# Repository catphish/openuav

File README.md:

# OpenUAV
OpenUAV is an open source flight controller for multirotors with
a focus on FPV. It is currently in active development.

# Features
* ACRO and ANGLE flight modes
* DSHOT
* ELRS
* Blackbox flight recorder
* USB configuration tool
* Canvas OSD

# Roadmap
* Tidy up and comment all current code
* USB configuration tool
* More OSD options

# Dependencies

## ArchLinux-based distributions

```sh
sudo pacman -Sy arm-none-eabi-binutils arm-none-eabi-gcc arm-none-eabi-newlib \
                dfu-util \
                stlink
```

# Configurator

The USB configurator can be used to configure the quad, and also to download blackbox
logs.

## Configuration

You can view the current configuration by running `configurator get`.

The commands to set configuration are a little cryptic. Use command `configurator set x y z`, where `x` is the
categry number, `y` is the specific entry number, and `z` is the value to set. Please refer to the following file
for the category and entry numbers: https://github.com/catphish/openuav/blob/master/configurator/usb.h

## Motor configuration

The motor configuration is also not very intuitive, but works as follows. First select "props in" `configurator set 3 5 0`
or "props out" `configurator set 3 5 1`.

Next, map the motor outputs using the command: `configurator set 3 x y`, where `x` is the motor output pin (1-4), and `y` is
a corner of the quad according to the following table:

```
0: no output
1: rear left
2: front right
3: front left
4: rear right
```

* NOTE: Due to the way air mode currently works, motors set to zero outout will still spin at minimum RPM. This needs fixing.

## Black Box

Data will be recorded to the black box any time the quad is armed and will continue until the memory
is full (approx 10 minutes flight time). You can erase the black box with `configurator erase`.

You can download the blackbox data with `configurator read > data.csv`. The CSV can be processed
with any tool of your choosing but I find kst2 to be the best.

# Basic Tuning Guide

Tuning should be done in acro mode at a rate you are comfortable with. I use a rate
of 1200 (840 dps) for this process.

## Part 1 - P term

Set the I and D terms to zero so that they don't interfere. Start with a low value (P=50).
Increase P until the quad is sufficiently responsive to stick inputs. You can expect a
little bounceback.
In the 5 inch development quad, the P value is 120.

## Part 2 - D term

Increase the D term only as much as is required to prevent the bounceback.
In the 5 inch development quad, the D value is 150.

## Part 3 - I term

Increase the I term only as much as is required to prevent drift. You may find that this
needs to be increased more when flying in strong wind. Higher values will make the quad
more stable but will introduce some bouncenback when performing flips.
In the 5 inch development quad, the I value is 50.

## Part 4 - Z rates

There is currently no specific process for tuning the Z rates. Values of 200 and 200
for P and I seem to work in most cases. If there is yaw drift then it may be necessary
to increase one or the other. Increase the I term in the case of slow drift or the P
term in the case of sudden yaw disruption.

# Tuning Examples

## TBS Source One V5 5" - 2306/2555KV Motors at 4S

```
Angle rate: 1000
Acro rate: 1000
P: 100
I: 80
D: 100
Yaw P: 200
Yaw I: 100
Expo: 60
Yaw expo: 60
Throttle gain: 80
Throttle min: 200
```

## iFlight iX3 Racer V1 3" - 1104/5250KV Motors at 3S

THIS TUNE IS STILL UNDERGOING TESTING

```
Angle rate (sR): 670
Acro rate (sr): 670
P (sp): x
I (si): x
D (sd): x
Yaw P (sy): 220
Yaw I (sY): 200
Expo (se): 25
Yaw expo (sE): 30
Throttle gain (st): 80
Throttle min (sT): 100
```

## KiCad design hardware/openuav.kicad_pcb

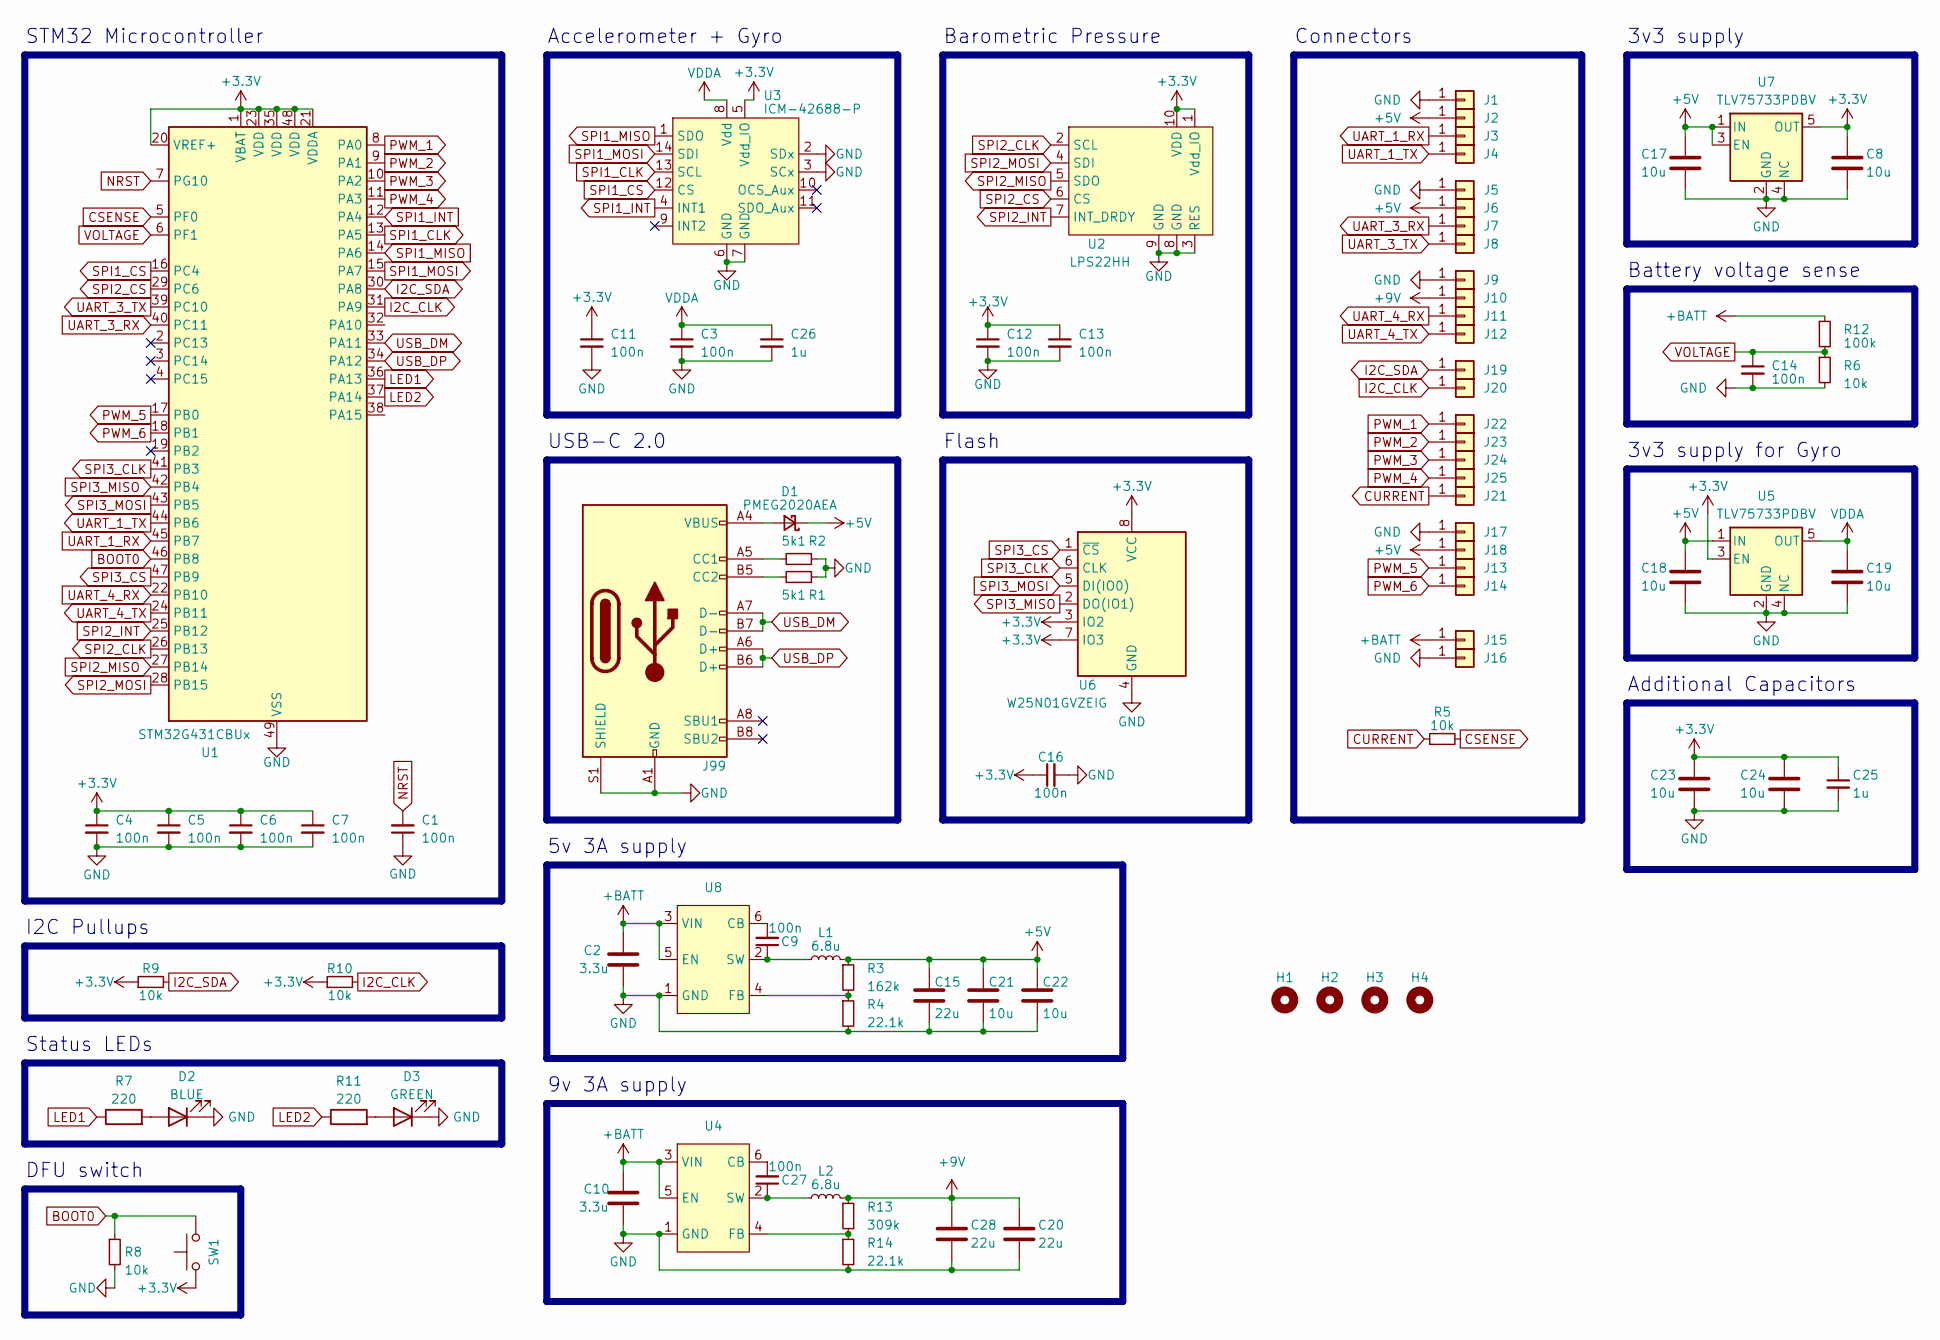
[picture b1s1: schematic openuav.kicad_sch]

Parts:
C1, C3, C4, C5, C6, C7, C9, C11, C12, C13, C14, C16, C27: 100n; C_0402_1005Metric; LCSC C1525
C2, C10: 3.3u; C_0805_2012Metric; LCSC C342775
C8, C17, C18, C19, C21, C22, C23, C24: 10u; C_0603_1608Metric; LCSC C19702
C15, C20, C28: 22u; C_0805_2012Metric; LCSC C45783
C25, C26: 1u; C_0402_1005Metric; LCSC C52923
D1: PMEG2020AEA; D_SOD-323; LCSC C389354
D2: BLUE; LED_0603_1608Metric; LCSC C72041
D3: GREEN; LED_0603_1608Metric; LCSC C2986059
H1, H2, H3, H4: MountingHole; MountingHole_4mm
J1, J2, J3, J4, J5, J6, J7, J8, J9, J10, J11, J12, J13, J14, J15, J16, J17, J18, J19, J20, J21, J22, J23, J24, J25: Conn_01x01; smallpad
J99: USB_C_Receptacle_USB2.0; TYPE-C-31-M-12; LCSC C165948
L1, L2: 6.8u; L_Sunlord_MWSA0402S; LCSC C408338
R1, R2: 5k1; R_0402_1005Metric; LCSC C25905
R3: 162k; R_0402_1005Metric; LCSC C185462
R4, R14: 22.1k; R_0402_1005Metric; LCSC C163478
R5, R6, R8, R9, R10: 10k; R_0402_1005Metric; LCSC C25744
R7, R11: 220; R_0603_1608Metric; LCSC C22962
R12: 100k; R_0402_1005Metric; LCSC C25741
R13: 309k; R_0402_1005Metric; LCSC C226980
SW1: SW_Push; SW_SPST_B3U-1000P; LCSC C231329
U1: STM32G431CBUx; QFN-48-1EP_7x7mm_P0.5mm_EP5.6x5.6mm; LCSC C529356
U2: LPS22HH; ST_HLGA-10_2x2mm_P0.5mm_LayoutBorder3x2y; LCSC C2827824
U3: ICM-42688-P; LGA-14_3x2.5mm_P0.5mm_LayoutBorder3x4y; LCSC C1850418
U4, U8: SOT-23-6; LCSC C5383002
U5, U7: TLV75733PDBV; SOT-23-5; LCSC C485517
U6: W25N01GVZEIG; WSON-8-1EP_8x6mm_P1.27mm_EP3.4x4.3mm; LCSC C907680

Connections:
+3V3: C4.1, C5.1, C6.1, C7.1, C8.1, C11.1, C12.1, C13.1, C16.1, C23.1, C24.1, C25.1, R9.1, R10.1, SW1.1, U1.1 (VBAT), U1.20 (VREF+), U1.21 (VDDA), U1.23 (VDD), U1.35 (VDD), U1.48 (VDD), U2.1 (Vdd_IO), U2.10 (VDD), U3.5 (Vdd_IO), U5.3 (EN), U6.3 (IO2), U6.7 (IO3), U6.8 (VCC), U7.5 (OUT)
+5V: C15.1, C17.1, C18.1, C21.1, C22.1, D1.1 (K), J2.1, J6.1, J18.1, L1.2, R3.1, U5.1 (IN), U7.1 (IN), U7.3 (EN)
+9V: C20.1, C28.1, J10.1, L2.2, R13.1
+BATT: C2.1, C10.1, J15.1, R12.1, U4.3 (VIN), U4.5 (EN), U8.3 (VIN), U8.5 (EN)
BOOT0: R8.1, SW1.2, U1.46 (PB8)
CSENSE: R5.2, U1.5 (PF0)
CURRENT: J21.1, R5.1
GND: C1.1, C2.2, C3.2, C4.2, C5.2, C6.2, C7.2, C8.2, C10.2, C11.2, C12.2, C13.2, C14.2, C15.2, C16.2, C17.2, C18.2, C19.2, C20.2, C21.2, C22.2, C23.2, C24.2, C25.2, C26.2, C28.2, D2.1 (K), D3.1 (K), J1.1, J5.1, J9.1, J16.1, J17.1, J99.A1 (GND), J99.A12 (GND), J99.B1 (GND), J99.B12 (GND), J99.S1 (SHIELD), R1.1, R2.1, R4.2, R6.2, R8.2, R14.2, U1.49 (VSS), U2.3 (RES), U2.8 (GND), U2.9 (GND), U3.2 (SDx), U3.3 (SCx), U3.6 (GND), U3.7 (GND), U4.1 (GND), U5.2 (GND), U5.4 (NC), U6.4 (GND), U7.2 (GND), U7.4 (NC), U8.1 (GND)
I2C_CLK: J20.1, R10.2, U1.31 (PA9)
I2C_SDA: J19.1, R9.2, U1.30 (PA8)
LED1: R7.1, U1.36 (PA13)
LED2: R11.1, U1.37 (PA14)
NRST: C1.2, U1.7 (PG10)
unnamed: D1.2 (A), J99.A4 (VBUS), J99.A9 (VBUS), J99.B4 (VBUS), J99.B9 (VBUS)
unnamed: D2.2 (A), R7.2
unnamed: D3.2 (A), R11.2
unnamed: J99.A5 (CC1), R2.2
unnamed: J99.B5 (CC2), R1.2
unnamed: C27.2, U4.6 (CB)
unnamed: R13.2, R14.1, U4.4 (FB)
unnamed: C27.1, L2.1, U4.2 (SW)
unnamed: C9.2, U8.6 (CB)
unnamed: R3.2, R4.1, U8.4 (FB)
unnamed: C9.1, L1.1, U8.2 (SW)
PWM_1: J22.1, U1.8 (PA0)
PWM_2: J23.1, U1.9 (PA1)
PWM_3: J24.1, U1.10 (PA2)
PWM_4: J25.1, U1.11 (PA3)
PWM_5: J13.1, U1.17 (PB0)
PWM_6: J14.1, U1.18 (PB1)
SPI1_CLK: U1.13 (PA5), U3.13 (SCL)
SPI1_CS: U1.16 (PC4), U3.12 (CS)
SPI1_INT: U1.12 (PA4), U3.4 (INT1)
SPI1_MISO: U1.14 (PA6), U3.1 (SDO)
SPI1_MOSI: U1.15 (PA7), U3.14 (SDI)
SPI2_CLK: U1.26 (PB13), U2.2 (SCL)
SPI2_CS: U1.29 (PC6), U2.6 (CS)
SPI2_INT: U1.25 (PB12), U2.7 (INT_DRDY)
SPI2_MISO: U1.27 (PB14), U2.5 (SDO)
SPI2_MOSI: U1.28 (PB15), U2.4 (SDI)
SPI3_CLK: U1.41 (PB3), U6.6 (CLK)
SPI3_CS: U1.47 (PB9), U6.1 (~CS)
SPI3_MISO: U1.42 (PB4), U6.2 (DO(IO1))
SPI3_MOSI: U1.43 (PB5), U6.5 (DI(IO0))
UART_1_RX: J3.1, U1.45 (PB7)
UART_1_TX: J4.1, U1.44 (PB6)
UART_3_RX: J7.1, U1.40 (PC11)
UART_3_TX: J8.1, U1.39 (PC10)
UART_4_RX: J11.1, U1.22 (PB10)
UART_4_TX: J12.1, U1.24 (PB11)
USB_DM: J99.A7 (D-), J99.B7 (D-), U1.33 (PA11)
USB_DP: J99.A6 (D+), J99.B6 (D+), U1.34 (PA12)
VDDA: C3.1, C19.1, C26.1, U3.8 (Vdd), U5.5 (OUT)
VOLTAGE: C14.1, R6.1, R12.2, U1.6 (PF1)

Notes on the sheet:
Accelerometer + Gyro
DFU switch
Status LEDs
3v3 supply
Additional Capacitors
5v 3A supply
Flash
Barometric Pressure
9v 3A supply
STM32 Microcontroller
Connectors
I2C Pullups
USB-C 2.0
Battery voltage sense
3v3 supply for Gyro

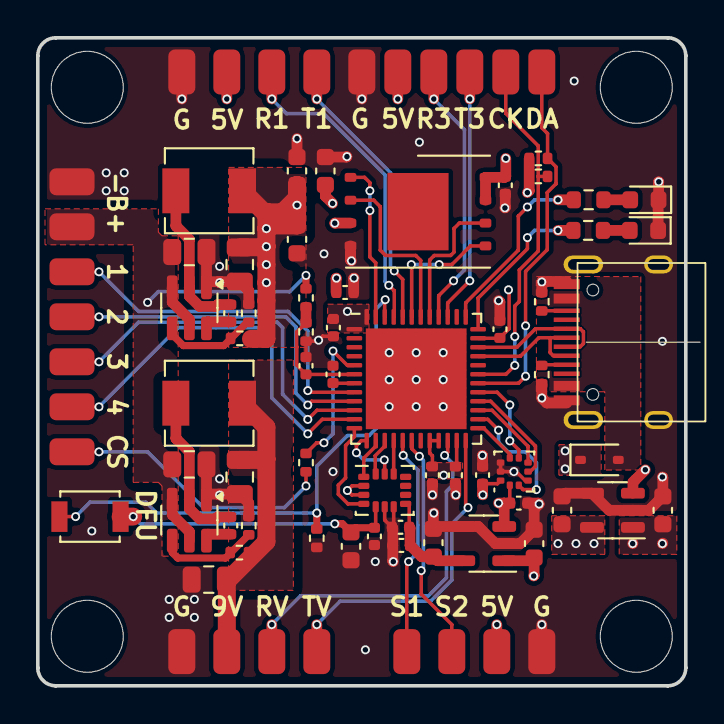
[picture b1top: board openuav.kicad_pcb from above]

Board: 4 copper layers, 36.0 x 36.0 mm, 86 parts (0 on the bottom side), 54 nets.

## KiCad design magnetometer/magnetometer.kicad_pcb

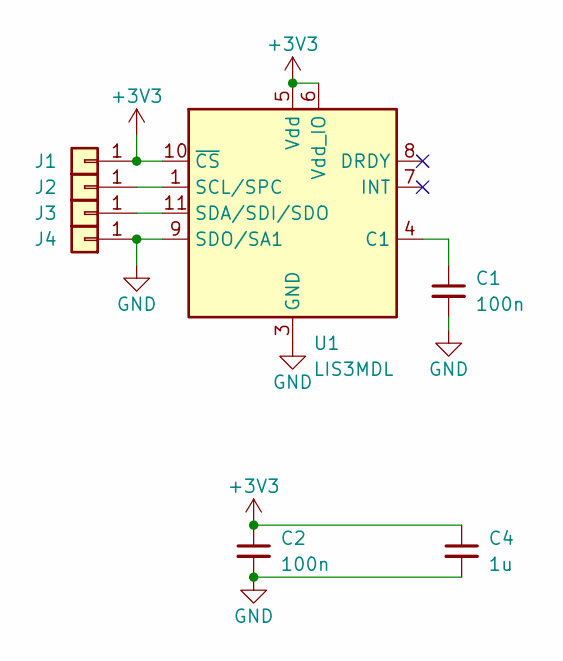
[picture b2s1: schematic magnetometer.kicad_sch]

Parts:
C1, C2: 100n; C_0402_1005Metric; LCSC C1525
C4: 1u; C_0402_1005Metric; LCSC C52923
J1, J2, J3, J4: Conn_01x01; smallpad
U1: LIS3MDL; LGA-12_2x2mm_P0.5mm; LCSC C478483

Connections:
+3V3: C2.1, C4.1, J1.1, U1.5 (Vdd), U1.6 (Vdd_IO), U1.10 (~CS)
GND: C1.2, C2.2, C4.2, J4.1, U1.2 (GND), U1.3 (GND), U1.9 (SDO/SA1), U1.12 (GND)
unnamed: J2.1, U1.1 (SCL/SPC)
unnamed: J3.1, U1.11 (SDA/SDI/SDO)
unnamed: C1.1, U1.4 (C1)

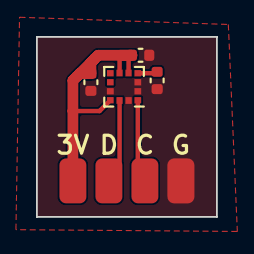
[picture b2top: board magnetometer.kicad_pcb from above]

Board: 2 copper layers, 10.0 x 10.0 mm, 8 parts (0 on the bottom side), 5 nets.

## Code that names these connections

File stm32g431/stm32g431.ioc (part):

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Mcu.Name=STM32G431C(6-8-B)Ux
Mcu.Package=UFQFPN48
Mcu.UserName=STM32G431CBUx
PA0.Signal=S_TIM2_CH1
PA1.Signal=S_TIM2_CH2
PA10.GPIOParameters=GPIO_Label
PA10.GPIO_Label=LED2
PA10.Signal=GPIO_Output
PA11.Mode=Device
PA11.Signal=USB_DM
PA12.Mode=Device
PA12.Signal=USB_DP
PA13.Mode=Serial_Wire
PA13.Signal=SYS_JTMS-SWDIO
PA14.Mode=Serial_Wire
PA14.Signal=SYS_JTCK-SWCLK
PA15.GPIOParameters=GPIO_Label
PA15.GPIO_Label=SPI3_CS
PA15.Signal=GPIO_Output
PA2.Signal=S_TIM2_CH3
PA3.Signal=S_TIM2_CH4
PA4.GPIOParameters=GPIO_Label
PA4.GPIO_Label=SPI1_INT
PA4.Signal=GPXTI4
PA5.Mode=Full_Duplex_Master
PA5.Signal=SPI1_SCK
PA6.Mode=Full_Duplex_Master
PA6.Signal=SPI1_MISO
PA7.Mode=Full_Duplex_Master
PA7.Signal=SPI1_MOSI
PA8.Mode=I2C
PA8.Signal=I2C2_SDA
PA9.Mode=I2C
PA9.Signal=I2C2_SCL
PB0.Signal=S_TIM3_CH3
PB1.Signal=S_TIM3_CH4
PB10.Mode=Asynchronous
PB10.Signal=LPUART1_RX
PB11.Mode=Asynchronous
PB11.Signal=LPUART1_TX
PB12.GPIOParameters=GPIO_Label
PB12.GPIO_Label=SPI2_INT
PB12.Signal=GPXTI12
PB13.Mode=Full_Duplex_Master
PB13.Signal=SPI2_SCK
PB14.Mode=Full_Duplex_Master
PB14.Signal=SPI2_MISO
PB15.Mode=Full_Duplex_Master
PB15.Signal=SPI2_MOSI
PB3.Mode=Full_Duplex_Master
PB3.Signal=SPI3_SCK
PB4.Mode=Full_Duplex_Master
PB4.Signal=SPI3_MISO
PB5.Mode=Full_Duplex_Master
PB5.Signal=SPI3_MOSI
PB6.Mode=Asynchronous
PB6.Signal=USART1_TX
PB7.Mode=Asynchronous
PB7.Signal=USART1_RX
PB9.GPIOParameters=GPIO_Label
PB9.GPIO_Label=LED1
PB9.Signal=GPIO_Output
PC10.Mode=Asynchronous
PC10.Signal=USART3_TX
PC11.Mode=Asynchronous
PC11.Signal=USART3_RX
PC4.GPIOParameters=GPIO_Label
PC4.GPIO_Label=SPI1_CS
PC4.Signal=GPIO_Output
PC6.GPIOParameters=GPIO_Label
PC6.GPIO_Label=SPI2_CS
PC6.Signal=GPIO_Output
PF0-OSC_IN.Mode=IN10-Single-Ended
PF0-OSC_IN.Signal=ADC1_IN10
PF1-OSC_OUT.Mode=IN10-Single-Ended
PF1-OSC_OUT.Signal=ADC2_IN10
RCC.HSE_VALUE=8000000
RCC.SYSCLKFreq_VALUE=160000000
RCC.SYSCLKSource=RCC_SYSCLKSOURCE_PLLCLK
board=custom

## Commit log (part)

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2023-04-19 Initial commit, dev board
2023-04-21 Work in progress on more complete schematic
2023-04-21 Continued work in progress on initial design
2023-04-21 Remove unused template
2023-04-21 Change OSD to 3v3, align pads to edge
2023-04-23 start to rethink power supplies
2023-04-23 remove power supply, start over
2023-04-24 Add new 5V SMPS. Rearrange MCU pins to support 3 x SPI
2023-04-24 Update README with current parts
2023-04-25 Begin basic firmware
2023-04-25 add basic CRSF receiver
2023-04-26 start adding i2c
2023-04-30 USART3 interrupts
2023-04-30 Finish blending ELRS and gyro into motors, split code out into files
2023-04-30 work on layout with JST-SH connectors
2023-05-01 finish basic board layout
2023-05-03 new PCB WIP
2023-05-04 Finish draft PCB design
2023-05-04 improved sinkscreen and readme
2023-05-04 tidying
2023-05-04 Add buzzer connection, minor layout improvements
2023-05-04 update schematic with buzzer
2023-05-04 increase density
2023-05-05 Improve connector spacing and thermal management
2023-05-05 tiny layout fix
2023-05-05 update ioc file with all pins, add pulldown on boot0
2023-05-05 final touches to pcb
2023-05-05 add note about TT pin
2023-05-05 Replace ST parts with BMI270 and BMP280
2023-05-05 Label pins in cubemx, remove redundant BARO interrupt pin label
2023-05-05 Add missing JLC part numbers
2023-05-05 Increase all vias to 0.3/0.5
2023-05-06 Remove unused connector 3D models
2023-05-06 add readme for firmware
2023-05-06 fix JLC 10k resistor part numbers
2023-05-17 continue g474 redesign
2023-05-17 continued work on G474 board
2023-05-17 routing
2023-05-18 continues work on G474 layout TODO: the pin space is 2.5mm not 2.54mm
2023-05-18 update schematic pdf and board image
2023-05-22 finish G474 layout, add buzzer buffer, add pullups, fix pin spacing
2023-05-22 add heatsink copper to inductor
2023-05-22 rearrange buzzer pins to keep +5v away from USB GND
2023-05-23 add vtx power switch, use smaller dfu button
2023-05-23 update render
2023-05-24 update schematic pdf
2023-06-06 Add missing connections on flash HOLD and WP pins Make 5V plane slightly larger in corners to make space for tooling holes
2023-06-10 Connect VREF+ to 3v3
2023-06-11 start work again on g431 board
2023-06-11 Remove old files
2023-06-11 major work on G431
2023-06-12 WIP on G431 layout
2023-06-12 more on g431 board
2023-06-13 finish g431 design
2023-06-13 add tiny i2c magnetometer board
2023-06-13 start over with firmware, work on usb driver
2023-06-14 implement dshot
2023-06-15 finish basis USB implementation
2023-06-15 planning lots more code
2023-06-26 Various firmware work
2023-06-27 improve usb driver with cdc acm support
2023-07-14 lots of work on firmware, dshot, gyro, elrs
2023-07-15 add integral term to gyro pid
2023-07-16 work in progress on angle
2023-07-17 more work in progress on angle
2023-07-17 Complete proof of concept for gyro+accelerometer leveling
2023-07-17 update README progress
2023-07-18 Use timer for gyro dt measurement
2023-07-18 Just a little tidying
2023-07-18 Optimize and reduce code size
2023-07-19 Begin barometer support
2023-07-19 Fix pin configuration for pin 8
2023-07-19 Add I2C and QMC5883L
2023-07-21 Fix power supply capacitor in schematic
2023-07-22 Fix typo
2023-07-22 Concept for compass integration
2023-07-22 Tidy up heading hold code a little
2023-07-22 Elaborate on comment
2023-07-22 Refactor throttle code
2023-07-23 Increase frequency to 833Hz, tune for F450, selectable rate/angle modes
2023-07-25 Run P and I calculations in parallel, tune and configure for 5 inch
2023-07-28 Add basic MSP implementation with hardcoded arming status
2023-07-28 Add D term and air mode
2023-07-28 Further Tuning for 5 inch
2023-07-28 Add OSD proof of concept
2023-07-28 Update progress in README
2023-07-28 Add 200ms delay at boot. ESCs get confused if we send DSHOT before they're ready.
2023-07-31 Fix LED polarity, move OSD out of interrupt and add voltage, more tuning
2023-07-31 Less extreme D gain
2023-07-31 Finish tune, increase rate a little
2023-08-01 remove unused code, fix timing
2023-08-01 Apply basic tune for 5 inch, remove D term
2023-08-01 Fix layout for SMPS feedback capacitor
2023-08-01 remove copper under inductor
2023-08-02 Make motor mappings and prop configuration much clearer. Improve voltage string handling.
2023-08-02 Rename pitch and roll variables for clarity. The gyro hardware calls the pitch axis X and the roll axis Y which I find confusing.
2023-08-02 Add GPS and WIP position hold (without compass)
2023-08-02 Remove magnetometer PCB, never really started
2023-08-02 GPS Position hold, a little tidying
2023-08-02 Tidy up GPS hold code a little
2023-08-02 for those if us who like to keep their tools close
2023-08-02 convenience changes:
    - var for path to elf2dfuse
    - alternatives for tool paths used by sixtyfive provided as comments
    - two different flash targets
2023-08-02 things that helped me get it working
2023-08-02 Add build info and tuning notes to README
2023-08-03 More on GPS and altitude hold
2023-08-03 Tidy up. Remove nav related code, this can be tracked separately.
2023-08-03 More aggressive 5 inch tune
2023-08-03 Final (for now) 5 inch tuning
2023-08-04 Require disarm before arm. Verify ELRS checksum.
2023-08-04 Add comment about rates. Begin USB configuration.
2023-08-04 Small PID change
2023-08-04 Configure gyro hardware filter to 100Hz, increase loop rate to 1667Hz
2023-08-04 Add D term
2023-08-05 Begin settings API
2023-08-05 Lots more work on USB configuration
2023-08-05 Expo rates prototype
2023-08-06 Finish USB config
2023-08-06 Display expo in settings dump
2023-08-06 Remove debug port
2023-08-10 Increase loop rate to 3.33kHz, enable gyro low pass filter
2023-08-10 update example tune to be sane for new loop rate
2023-08-12 Work in progress on new power supplies
2023-08-12 Update example PID
2023-08-12 Implement air mode better
2023-08-12 Reduce filter cutoff to 170.1Hz
2023-08-12 Update sample config again for new filtering
2023-08-12 More work on 36V power supplies
2023-08-12 Revert "Work in progress on new power supplies"
    This reverts commit f380e0b659656c6729afb5916a220a1607aef7b0.
2023-08-13 Use high speed IO for SPI pins. Begin flash interface.
2023-08-13 More on flash memory
2023-08-14 Add dual 9v / 5v power supplies
2023-08-15 Add remaining part numbers, temporarily downgrade baro due to availability
2023-08-15 Slightly higher filter cutoff
2023-08-15 Update 5 inch rates to match current tunig efforts
2023-08-16 Begin blackbox
2023-08-16 lots of work on blackbox logging
2023-08-17 various changes to blackbox, try out more aggressive low pass filter
2023-08-17 revert experimental gyro settings, add D term filter
2023-08-18 Change 9V enable resistor to pull-down
2023-08-18 Update part number for baro
2023-08-19 Tidying and commenting. This is untested but shouldn't contain any functional changes.
2023-08-19 add WIP tune for Toadie
2023-08-19 add WIP tune for Toadie (#6)
2023-08-20 Implement software gyro filtering and improved D term
2023-08-20 Update README to reflect new filters
2023-08-20 program ADC h/w directly
2023-08-20 rename adc read; get coefficient from settings
2023-08-20 enable 256x oversampling, yeah
2023-08-20 make it possible to set cell count manually
2023-08-20 comments and some boyscouting
2023-08-20 respond to review comments
2023-08-20 fix 256x oversampling parts
2023-08-20 adjust to 5MHz-clocked ADC code
2023-08-20 display "armed" or "disarmed"
2023-08-20 probably more sensible order of things
2023-08-20 whoops!
2023-08-20 Move hardware design into a directory
2023-08-20 Improve ADC configuration and add cell count estimator
2023-08-20 Add three new OSD features:
    - one-letter indicator for armed/disarmed state
    - one-letter indicator for acro/angle mode
    - display "BATTERY!" in the middle of the screen once the voltage
    drops too much
2023-08-21 Update IMU calculations to reflect higher update rate and use unfiltered gyro data
2023-08-25 Add MIT license
2023-08-26 more updates for v1 hardware
2023-08-26 Remove SMPS in preparation for next attempt
2023-08-26 Update LEDs for v2 board, rework USB interface
2023-08-26 Fix elrs call
2023-08-26 Begin TI SMPS design
2023-08-26 Work in progress new SMPS
2023-08-26 Add defines for v1/v2/v3 board compatibility
2023-08-26 Set v1 board constants
2023-08-26 Revert v1 hardware, remove unused code for v2 hardware
2023-08-27 Increase board size
2023-08-27 Remove reset button
2023-08-27 Move pads to edge of board
2023-08-27 Swap USB power diode for smaller part
2023-08-27 Finish v3 board design
2023-08-27 Continued work on configurator. Add missing blackbox_init call.
2023-08-27 Move filter coefficients to new file
2023-08-27 Enable compiler optimizations
2023-08-27 Rework supply rail capacitors
2023-08-27 Replace LSM6DSO with LSM6DSR
2023-08-27 Move README, negligable PCB layout improvement
2023-08-28 Add full config dump to configurator
2023-08-28 Add longer gyro calibration routine
2023-08-30 Slight changes to configurator CSV processing
2023-08-30 Log raw gyro data
2023-09-02 Move filter code to its own module
2023-09-02 Remove cell count guess and replace with configuration option
2023-09-02 Fixes for new gyro filtering changes
2023-09-02 Change cell chcmistry to cell count, remove old code from configurator
2023-09-02 Add comments
2023-09-02 Remove software gyro filters, implement simpler D term filter.
2023-09-02 Change D term scaling and update readme
2023-09-02 Change ADC calibration to be more intuitive
2023-09-02 Update tuning example
2023-09-02 Update README with clearer tuning guide
2023-09-02 Add basic configurator documentation to README
2023-09-04 Reduce optimization, O2 seems to cause intermittent problems with erasing flash
2023-09-06 Increase D term period. Add I term reduction during movements.
2023-09-09 Fix overflow in PID CSV export
2023-09-09 Change IMU to ICM-42688-P. Change top and bottom planes to GND.
2023-09-11 PCB improvements
2023-09-11 Recude loop rate to 833Hz
2023-09-11 Output blackbox time in seconds
2023-09-16 Begin ESC hardware
2023-09-17 Continued work on ESC
2023-09-18 Fix time output in configurator
2023-09-18 Basic driver for ICM-42688-P
2023-09-19 Change gyro rate to 8k
2023-09-21 Change order of parameters in output to match IDs
2023-09-21 Enable ICM-42688-P accelerometer, calibrate IMU for new gyro
2023-09-21 Fix time scaling in blackbox output
2023-09-22 Tidying, comments, refactoring, don't apply air mode to disabled motors
2023-09-22 Standardize all indentation to two spaces
2023-09-23 Update example tune for new gyro, change air mode to avoid motors stopping in extreme cases
2023-09-23 Remove ESC for now
2023-10-11 Add M10 GPS support This doesn't affect flight in any way yet but if a M10 GPS is connected, the power LED will flash and then turn solid when a 7-satellite lock is achieved. It exposes LAT and LONG 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
2023-10-11 Add barometer support This doesn't do anything yet but the data is now available for OSD and/or flight use.
2023-10-11 Begin reworking angle mode for better feel and configurability
2023-10-12 Add some comments to new angle code
2023-10-14 Current scaling in Amps and raw ADC data over USB
    - change adc_c to adc2_c everywhere
    - introduce 2nd coefficient for ADC1
    - submit ADC1/2 raw values over USB
    - display ADC1/2 raw values in configurator
    - ignore data files in configurator directory
2023-10-14 add changes missing from previous PR
2023-10-14 Fixes to current display code
2023-10-14 make configurator output a little more verbose
2023-10-14 make the flight mode more legible
2023-10-18 Add missing newline at end of "get" output.
2024-03-17 Switch buck chip to LMR51420Y, add 9V SMPS.
